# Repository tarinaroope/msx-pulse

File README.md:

# msx-pulse

A diagnostic cartridge for MSX computers. Very much a work in progress. This is at
proof-of-concept stage. It boots, it reads the bus, it tells you things, but it's a
long way from a finished product. I'm building it partly because I wanted an "is this
MSX dead, and if so why" tool, and partly to learn, so expect rough edges.

## What it does today

Plug it into the cartridge slot and it sits there passively. It doesn't drive the bus,
so it's safe to leave in while the MSX powers up on its own. While it watches, it
reports on a small OLED:

- the +5V, +12V and −12V rails
- whether the 3.58 MHz clock is alive and roughly the right frequency
- the state of /RESET
- what the address and data lines are doing, including bits that look stuck or are
  never driven

It can also pulse /RESET and follow the early boot sequence to see how far the machine
gets. There's a USB serial log too if you want the detail on a host.

That's already enough to tell, say, a dead clock apart from dead RAM without pulling
the machine apart. I'm still working out the full list of faults it can sensibly
diagnose and a lot of that will come from pointing it at actually-broken machines and
seeing what shows up.

## What's next

The next goal is to have the cartridge *serve* a diagnostic ROM to the MSX and act as
the boot ROM itself and run Z80 test code on the machine's own CPU, the way the Dead
Test cart does. The firmware already has the groundwork for this (it can emulate a ROM
on the bus), but turning that into a proper guided test sequence is the next chunk of
work. The passive monitoring above is the part that somewhat works.

## Hardware

Fair warning: I'm a software person, not a hardware engineer, and this board is one of
the first things I've designed. It's a quick first cut to get *something* I could test
firmware against, and it shows. There's a KiCad project in [`hardware/`](hardware/)
(schematics, PCB, gerbers) and a parts list in [`docs/BOM.csv`](docs/BOM.csv) — read
them as "what I actually had made", not "the right way to do this".

The brain is a bare RP2354B (the QFN-80 part, 48 GPIO, 2 MB internal flash) wired onto
the cartridge edge connector and powered from the slot. The current board puts 74LVC245
level shifters on just about every bus line. Having lived with it, I think that's
overkill... the address and control inputs could most likely get by with plain series
resistors and no shifters. The data lines are the exception: those are bidirectional
and actually get driven, so keeping real level shifting there still makes sense, mostly
for protection.

Things I'd like to change in the next board revision:

- drop the level shifters on the address/control inputs, keep them on D0–D7
- shrink the PCB to fit an actual MSX cartridge shell (it's oversized right now)
- swap the ADC protection diodes as I miscalculated the zeners, seems it works even better without.
- a bigger power-on-reset cap for a more reliable cold boot
- a normal 2.54 mm SWD header (plus a UART header which I omitted) instead of the fine-pitch one I used

## Building

You'll need the Arm GNU toolchain (`arm-none-eabi`), the Raspberry Pi Pico SDK, and
sjasmplus for the Z80 side.

```sh
export PICO_SDK_PATH=/path/to/pico-sdk
cmake -S . -B build -DPICO_TOOLCHAIN_PATH=/path/to/arm-none-eabi/bin
cmake --build build -j
```

Out comes:

- `build/src/firmware/msxdoc.uf2` — the firmware
- `build/diag.rom` — the Z80 test ROM, assembled and baked into the firmware for you (not served) 

## Flashing

Hold BOOTSEL, plug into USB, and drop the `.uf2` onto the drive that appears. Or, with
picotool:

```sh
picotool load -x build/src/firmware/msxdoc.uf2
```

Or via swd.

## Layout

```
src/rom/        Z80 test ROM (sjasmplus)
src/firmware/   RP2354B firmware (pico-sdk, C + PIO)
hardware/       KiCad schematics, PCB, gerbers
docs/           bill of materials
```

## License

MIT — see [LICENSE](LICENSE).

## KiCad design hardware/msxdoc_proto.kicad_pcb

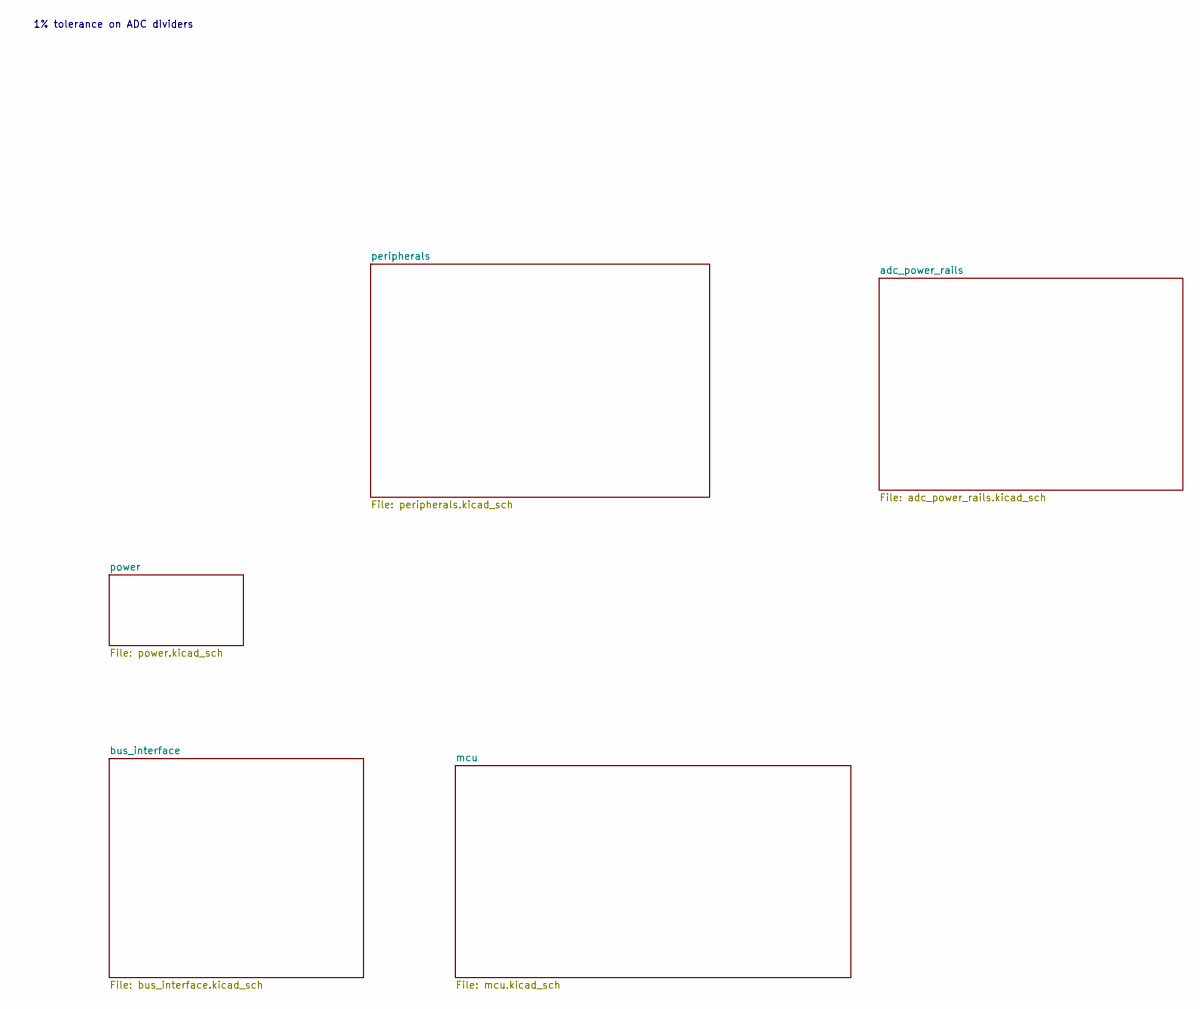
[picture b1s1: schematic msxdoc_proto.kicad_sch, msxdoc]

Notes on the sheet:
1% tolerance on ADC dividers

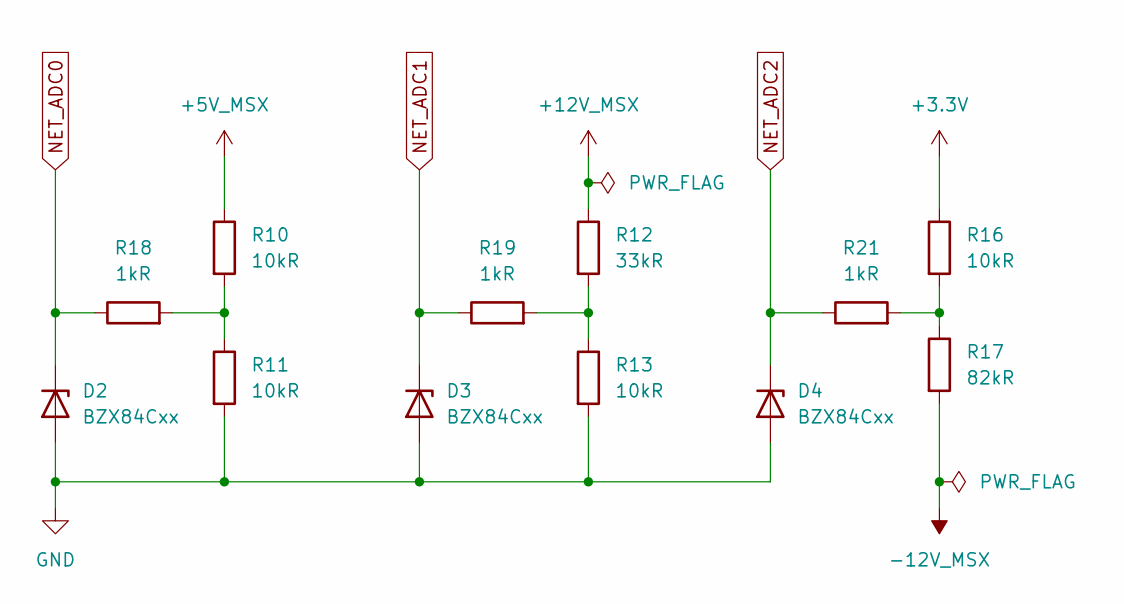
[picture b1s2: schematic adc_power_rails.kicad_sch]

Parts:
D2, D3, D4: BZX84Cxx; SOT-23
R10, R11, R13, R16: 10kR; R_0603_1608Metric
R12: 33kR; R_0603_1608Metric
R17: 82kR; R_0603_1608Metric
R18, R19, R21: 1kR; R_0603_1608Metric

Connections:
+3.3V: R16.1; also elsewhere on the board
+5V_MSX: R10.1; also elsewhere on the board
+12V_MSX: R12.1; also elsewhere on the board
-12V_MSX: R17.2; also elsewhere on the board
GND: D2.1 (A), D3.1 (A), D4.1 (A), R11.2, R13.2; also elsewhere on the board
NET_ADC0: D2.3 (K), R18.1; also elsewhere on the board
NET_ADC1: D3.3 (K), R19.1; also elsewhere on the board
NET_ADC2: D4.3 (K), R21.1; also elsewhere on the board
unnamed: R10.2, R11.1, R18.2
unnamed: R12.2, R13.1, R19.2
unnamed: R16.2, R17.1, R21.2

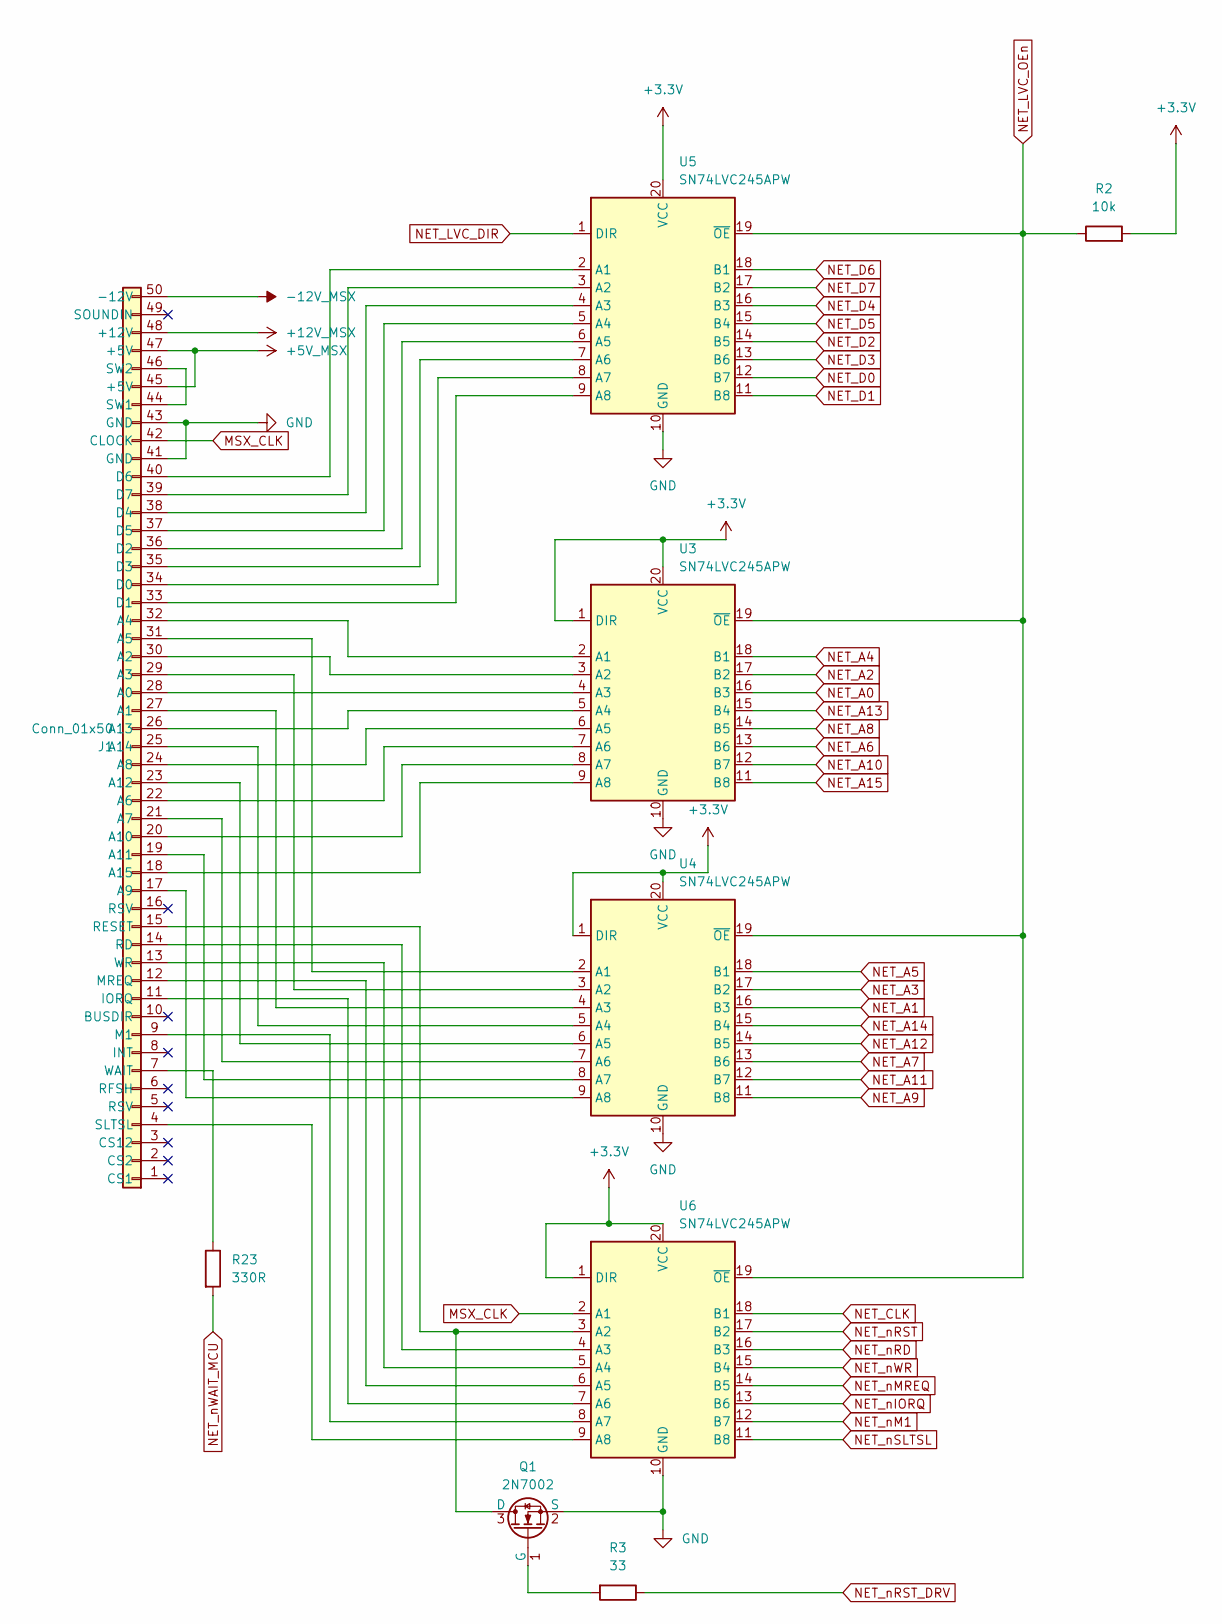
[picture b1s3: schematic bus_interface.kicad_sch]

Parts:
J1: Conn_01x50; MSX-EDGE
Q1: 2N7002; SOT-23; LCSC C81445
R2: 10k; R_0603_1608Metric
R3: 33; R_0603_1608Metric
R23: 330R; R_0603_1608Metric
U3, U4, U5, U6: SN74LVC245APW; TSSOP-20_4.4x6.5mm_P0.65mm; LCSC C7848

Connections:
+3.3V: R2.2, U3.1 (DIR), U3.20 (VCC), U4.1 (DIR), U4.20 (VCC), U5.20 (VCC), U6.1 (DIR), U6.20 (VCC); also elsewhere on the board
+5V_MSX: J1.45 (+5V), J1.47 (+5V); also elsewhere on the board
+12V_MSX: J1.48 (+12V); also elsewhere on the board
-12V_MSX: J1.50 (-12V); also elsewhere on the board
GND: J1.41 (GND), J1.43 (GND), Q1.2 (S), U3.10 (GND), U4.10 (GND), U5.10 (GND), U6.10 (GND); also elsewhere on the board
MSX_CLK: J1.42 (CLOCK), U6.2 (A1)
NET_A0: U3.16 (B3); also elsewhere on the board
NET_A1: U4.16 (B3); also elsewhere on the board
NET_A2: U3.17 (B2); also elsewhere on the board
NET_A3: U4.17 (B2); also elsewhere on the board
NET_A4: U3.18 (B1); also elsewhere on the board
NET_A5: U4.18 (B1); also elsewhere on the board
NET_A6: U3.13 (B6); also elsewhere on the board
NET_A7: U4.13 (B6); also elsewhere on the board
NET_A8: U3.14 (B5); also elsewhere on the board
NET_A9: U4.11 (B8); also elsewhere on the board
NET_A10: U3.12 (B7); also elsewhere on the board
NET_A11: U4.12 (B7); also elsewhere on the board
NET_A12: U4.14 (B5); also elsewhere on the board
NET_A13: U3.15 (B4); also elsewhere on the board
NET_A14: U4.15 (B4); also elsewhere on the board
NET_A15: U3.11 (B8); also elsewhere on the board
NET_CLK: U6.18 (B1); also elsewhere on the board
NET_D0: U5.12 (B7); also elsewhere on the board
NET_D1: U5.11 (B8); also elsewhere on the board
NET_D2: U5.14 (B5); also elsewhere on the board
NET_D3: U5.13 (B6); also elsewhere on the board
NET_D4: U5.16 (B3); also elsewhere on the board
NET_D5: U5.15 (B4); also elsewhere on the board
NET_D6: U5.18 (B1); also elsewhere on the board
NET_D7: U5.17 (B2); also elsewhere on the board
NET_LVC_DIR: U5.1 (DIR); also elsewhere on the board
NET_LVC_OEn: R2.1, U3.19 (~OE), U4.19 (~OE), U5.19 (~OE), U6.19 (~OE); also elsewhere on the board
NET_nIORQ: U6.13 (B6); also elsewhere on the board
NET_nM1: U6.12 (B7); also elsewhere on the board
NET_nMREQ: U6.14 (B5); also elsewhere on the board
NET_nRD: U6.16 (B3); also elsewhere on the board
NET_nRST: U6.17 (B2); also elsewhere on the board
NET_nRST_DRV: R3.1; also elsewhere on the board
NET_nSLTSL: U6.11 (B8); also elsewhere on the board
NET_nWAIT_MCU: R23.2; also elsewhere on the board
NET_nWR: U6.15 (B4); also elsewhere on the board
unnamed: J1.28 (A0), U3.4 (A3)
unnamed: J1.27 (A1), U4.4 (A3)
unnamed: J1.30 (A2), U3.3 (A2)
unnamed: J1.29 (A3), U4.3 (A2)
unnamed: J1.32 (A4), U3.2 (A1)
unnamed: J1.31 (A5), U4.2 (A1)
unnamed: J1.22 (A6), U3.7 (A6)
unnamed: J1.21 (A7), U4.7 (A6)
unnamed: J1.24 (A8), U3.6 (A5)
unnamed: J1.17 (A9), U4.9 (A8)
unnamed: J1.20 (A10), U3.8 (A7)
unnamed: J1.19 (A11), U4.8 (A7)
unnamed: J1.23 (A12), U4.6 (A5)
unnamed: J1.26 (A13), U3.5 (A4)
unnamed: J1.25 (A14), U4.5 (A4)
unnamed: J1.18 (A15), U3.9 (A8)
unnamed: J1.34 (D0), U5.8 (A7)
unnamed: J1.33 (D1), U5.9 (A8)
unnamed: J1.36 (D2), U5.6 (A5)
unnamed: J1.35 (D3), U5.7 (A6)
unnamed: J1.38 (D4), U5.4 (A3)
unnamed: J1.37 (D5), U5.5 (A4)
unnamed: J1.40 (D6), U5.2 (A1)
unnamed: J1.39 (D7), U5.3 (A2)
unnamed: J1.11 (IORQ), U6.7 (A6)
unnamed: J1.9 (M1), U6.8 (A7)
unnamed: J1.12 (MREQ), U6.6 (A5)
unnamed: J1.14 (RD), U6.4 (A3)
unnamed: J1.15 (RESET), Q1.3 (D), U6.3 (A2)
unnamed: J1.4 (SLTSL), U6.9 (A8)
unnamed: J1.44 (SW1), J1.46 (SW2)
unnamed: J1.7 (WAIT), R23.1
unnamed: J1.13 (WR), U6.5 (A4)
unnamed: Q1.1 (G), R3.2

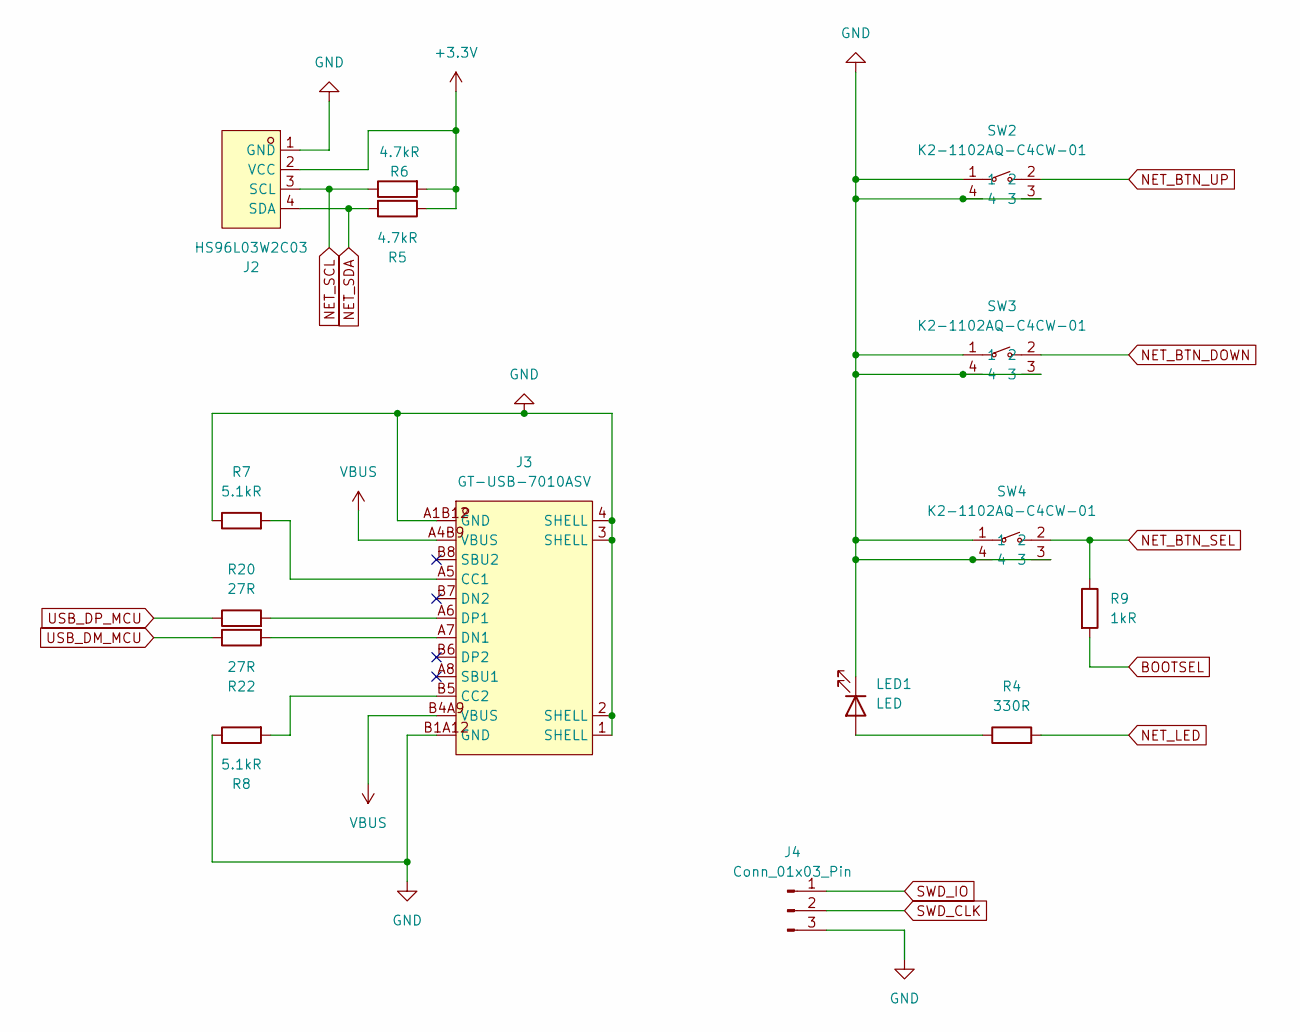
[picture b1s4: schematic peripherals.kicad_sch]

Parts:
J2: HS96L03W2C03; OLED-TH_L27.8-W27.2-P2.54_C9900033791; MPN HS96L03W2C03; LCSC Part C5248080
J3: GT-USB-7010ASV; USB-C-SMD_G-SWITCH_GT-USB-7010ASV; MPN GT-USB-7010ASV; LCSC Part C2988369
J4: Conn_01x03_Pin; PinHeader_1x03_P2.54mm_Vertical
LED1: LED; LED_0603_1608Metric
R4: 330R; R_0603_1608Metric
R5, R6: 4.7kR; R_0603_1608Metric
R7, R8: 5.1kR; R_0603_1608Metric
R9: 1kR; R_0603_1608Metric
R20, R22: 27R; R_0603_1608Metric
SW2, SW3, SW4: K2-1102AQ-C4CW-01; SW-TH_K2-1102AQ-C4CW-01; MPN K2-1102AQ-C4CW-01; LCSC Part C127680

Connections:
+3.3V: J2.2 (VCC), R5.1, R6.2; also elsewhere on the board
BOOTSEL: R9.2; also elsewhere on the board
GND: J2.1 (GND), J3.1 (SHELL), J3.2 (SHELL), J3.3 (SHELL), J3.4 (SHELL), J3.A1B12 (GND), J3.B1A12 (GND), J4.3, LED1.1 (K), R7.1, R8.1, SW2.1, SW2.3, SW2.4, SW3.1, SW3.3, SW3.4, SW4.1, SW4.3, SW4.4; also elsewhere on the board
NET_BTN_DOWN: SW3.2; also elsewhere on the board
NET_BTN_SEL: R9.1, SW4.2; also elsewhere on the board
NET_BTN_UP: SW2.2; also elsewhere on the board
NET_LED: R4.2; also elsewhere on the board
NET_SCL: J2.3 (SCL), R6.1; also elsewhere on the board
NET_SDA: J2.4 (SDA), R5.2; also elsewhere on the board
unnamed: J3.A5 (CC1), R7.2
unnamed: J3.B5 (CC2), R8.2
unnamed: J3.A7 (DN1), R22.2
unnamed: J3.A6 (DP1), R20.2
unnamed: LED1.2 (A), R4.1
SWD_CLK: J4.2; also elsewhere on the board
SWD_IO: J4.1; also elsewhere on the board
USB_DM_MCU: R22.1; also elsewhere on the board
USB_DP_MCU: R20.1; also elsewhere on the board
VBUS: J3.A4B9 (VBUS), J3.B4A9 (VBUS); also elsewhere on the board

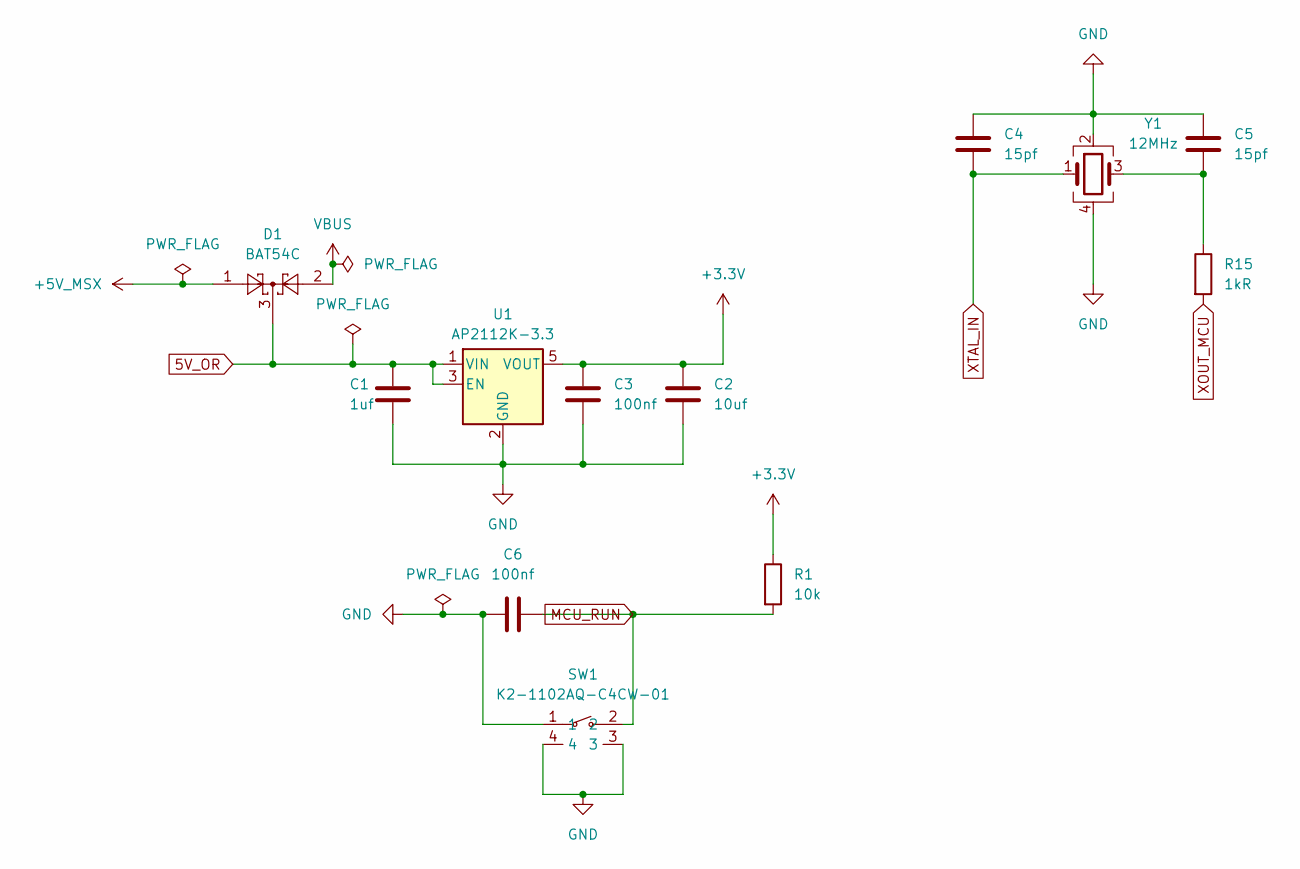
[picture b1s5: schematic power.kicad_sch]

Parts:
C1: 1uf; C_0603_1608Metric
C2: 10uf; C_0603_1608Metric
C3, C6: 100nf; C_0603_1608Metric
C4, C5: 15pf; C_0603_1608Metric
D1: BAT54C; SOT-23; LCSC C37704
R1: 10k; R_0603_1608Metric
R15: 1kR; R_0603_1608Metric
SW1: K2-1102AQ-C4CW-01; SW-TH_K2-1102AQ-C4CW-01; MPN K2-1102AQ-C4CW-01; LCSC Part C127680
U1: AP2112K-3.3; SOT-23-5; LCSC C23380830
Y1: 12MHz; Crystal_SMD_3225-4Pin_3.2x2.5mm; LCSC part C20625731

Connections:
5V_OR: C1.1, D1.3, U1.1 (VIN), U1.3 (EN)
+3.3V: C2.1, C3.1, R1.1, U1.5 (VOUT); also elsewhere on the board
+5V_MSX: D1.1; also elsewhere on the board
GND: C1.2, C2.2, C3.2, C4.1, C5.1, C6.1, SW1.1, SW1.3, SW1.4, U1.2 (GND), Y1.2, Y1.4; also elsewhere on the board
MCU_RUN: C6.2, R1.2, SW1.2; also elsewhere on the board
unnamed: C5.2, R15.1, Y1.3
VBUS: D1.2; also elsewhere on the board
XOUT_MCU: R15.2; also elsewhere on the board
XTAL_IN: C4.2, Y1.1; also elsewhere on the board

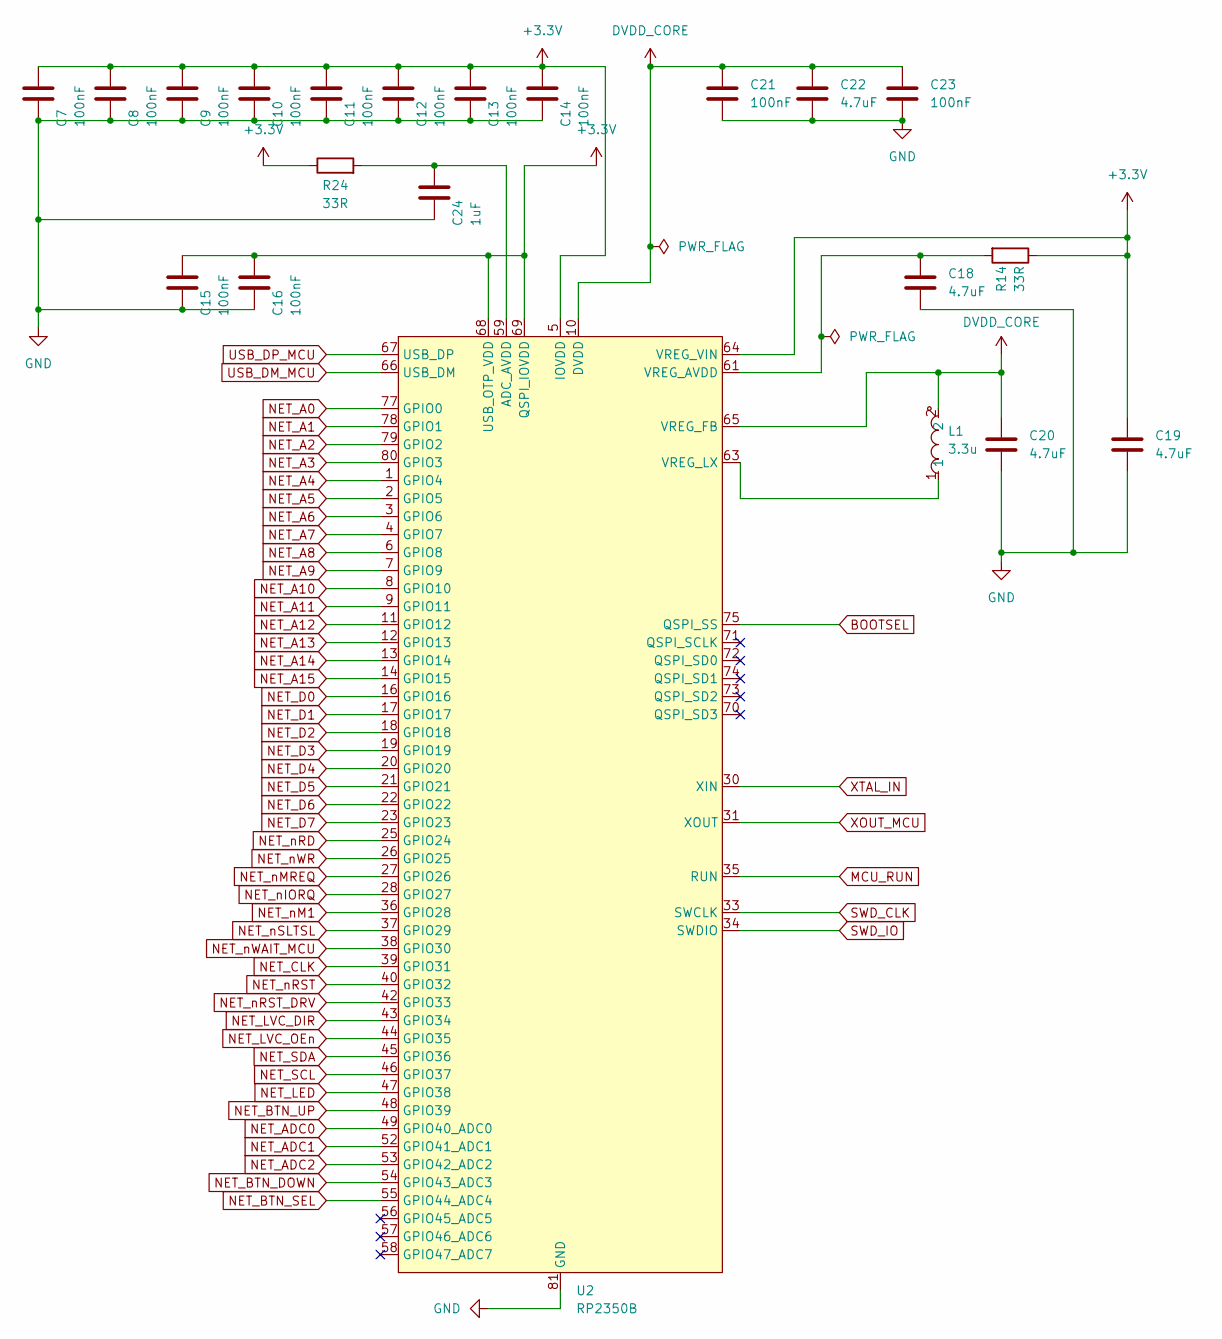
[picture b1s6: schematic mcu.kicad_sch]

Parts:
C7, C8, C9, C10, C11, C12, C13, C14, C15, C16, C21, C23: 100nF; C_0402_1005Metric
C18, C19, C20, C22: 4.7uF; C_0402_1005Metric
C24: 1uF; C_0402_1005Metric
L1: 3.3u; IND-SMD_L2.0-W1.6_AOTA-B201610S3R3-101-T; MPN AOTA-B201610S3R3-101-T; LCSC Part C42411119
R14, R24: 33R; R_0603_1608Metric
U2: RP2350B; QFN-80-1EP_10x10mm_P0.4mm_EP3.4x3.4mm_ThermalVias

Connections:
+3.3V: C7.1, C8.1, C9.1, C10.1, C11.1, C12.1, C13.1, C14.1, C15.1, C16.1, C19.1, R14.1, R24.1, U2.5 (IOVDD), U2.15 (IOVDD), U2.24 (IOVDD), U2.29 (IOVDD), U2.41 (IOVDD), U2.50 (IOVDD), U2.60 (IOVDD), U2.64 (VREG_VIN), U2.68 (USB_OTP_VDD), U2.69 (QSPI_IOVDD), U2.76 (IOVDD); also elsewhere on the board
BOOTSEL: U2.75 (QSPI_SS); also elsewhere on the board
DVDD_CORE: C20.1, C21.1, C22.1, C23.1, L1.2, U2.10 (DVDD), U2.32 (DVDD), U2.51 (DVDD), U2.65 (VREG_FB)
GND: C7.2, C8.2, C9.2, C10.2, C11.2, C12.2, C13.2, C14.2, C15.2, C16.2, C18.2, C19.2, C20.2, C21.2, C22.2, C23.2, C24.2, U2.62 (VREG_PGND), U2.81 (GND); also elsewhere on the board
MCU_RUN: U2.35 (RUN); also elsewhere on the board
NET_A0: U2.77 (GPIO0); also elsewhere on the board
NET_A1: U2.78 (GPIO1); also elsewhere on the board
NET_A2: U2.79 (GPIO2); also elsewhere on the board
NET_A3: U2.80 (GPIO3); also elsewhere on the board
NET_A4: U2.1 (GPIO4); also elsewhere on the board
NET_A5: U2.2 (GPIO5); also elsewhere on the board
NET_A6: U2.3 (GPIO6); also elsewhere on the board
NET_A7: U2.4 (GPIO7); also elsewhere on the board
NET_A8: U2.6 (GPIO8); also elsewhere on the board
NET_A9: U2.7 (GPIO9); also elsewhere on the board
NET_A10: U2.8 (GPIO10); also elsewhere on the board
NET_A11: U2.9 (GPIO11); also elsewhere on the board
NET_A12: U2.11 (GPIO12); also elsewhere on the board
NET_A13: U2.12 (GPIO13); also elsewhere on the board
NET_A14: U2.13 (GPIO14); also elsewhere on the board
NET_A15: U2.14 (GPIO15); also elsewhere on the board
NET_ADC0: U2.49 (GPIO40_ADC0); also elsewhere on the board
NET_ADC1: U2.52 (GPIO41_ADC1); also elsewhere on the board
NET_ADC2: U2.53 (GPIO42_ADC2); also elsewhere on the board
NET_BTN_DOWN: U2.54 (GPIO43_ADC3); also elsewhere on the board
NET_BTN_SEL: U2.55 (GPIO44_ADC4); also elsewhere on the board
NET_BTN_UP: U2.48 (GPIO39); also elsewhere on the board
NET_CLK: U2.39 (GPIO31); also elsewhere on the board
NET_D0: U2.16 (GPIO16); also elsewhere on the board
NET_D1: U2.17 (GPIO17); also elsewhere on the board
NET_D2: U2.18 (GPIO18); also elsewhere on the board
NET_D3: U2.19 (GPIO19); also elsewhere on the board
NET_D4: U2.20 (GPIO20); also elsewhere on the board
NET_D5: U2.21 (GPIO21); also elsewhere on the board
NET_D6: U2.22 (GPIO22); also elsewhere on the board
NET_D7: U2.23 (GPIO23); also elsewhere on the board
NET_LED: U2.47 (GPIO38); also elsewhere on the board
NET_LVC_DIR: U2.43 (GPIO34); also elsewhere on the board
NET_LVC_OEn: U2.44 (GPIO35); also elsewhere on the board
NET_SCL: U2.46 (GPIO37); also elsewhere on the board
NET_SDA: U2.45 (GPIO36); also elsewhere on the board
NET_nIORQ: U2.28 (GPIO27); also elsewhere on the board
NET_nM1: U2.36 (GPIO28); also elsewhere on the board
NET_nMREQ: U2.27 (GPIO26); also elsewhere on the board
NET_nRD: U2.25 (GPIO24); also elsewhere on the board
NET_nRST: U2.40 (GPIO32); also elsewhere on the board
NET_nRST_DRV: U2.42 (GPIO33); also elsewhere on the board
NET_nSLTSL: U2.37 (GPIO29); also elsewhere on the board
NET_nWAIT_MCU: U2.38 (GPIO30); also elsewhere on the board
NET_nWR: U2.26 (GPIO25); also elsewhere on the board
unnamed: C24.1, R24.2, U2.59 (ADC_AVDD)
unnamed: C18.1, R14.2, U2.61 (VREG_AVDD)
unnamed: L1.1, U2.63 (VREG_LX)
SWD_CLK: U2.33 (SWCLK); also elsewhere on the board
SWD_IO: U2.34 (SWDIO); also elsewhere on the board
USB_DM_MCU: U2.66 (USB_DM); also elsewhere on the board
USB_DP_MCU: U2.67 (USB_DP); also elsewhere on the board
XOUT_MCU: U2.31 (XOUT); also elsewhere on the board
XTAL_IN: U2.30 (XIN); also elsewhere on the board

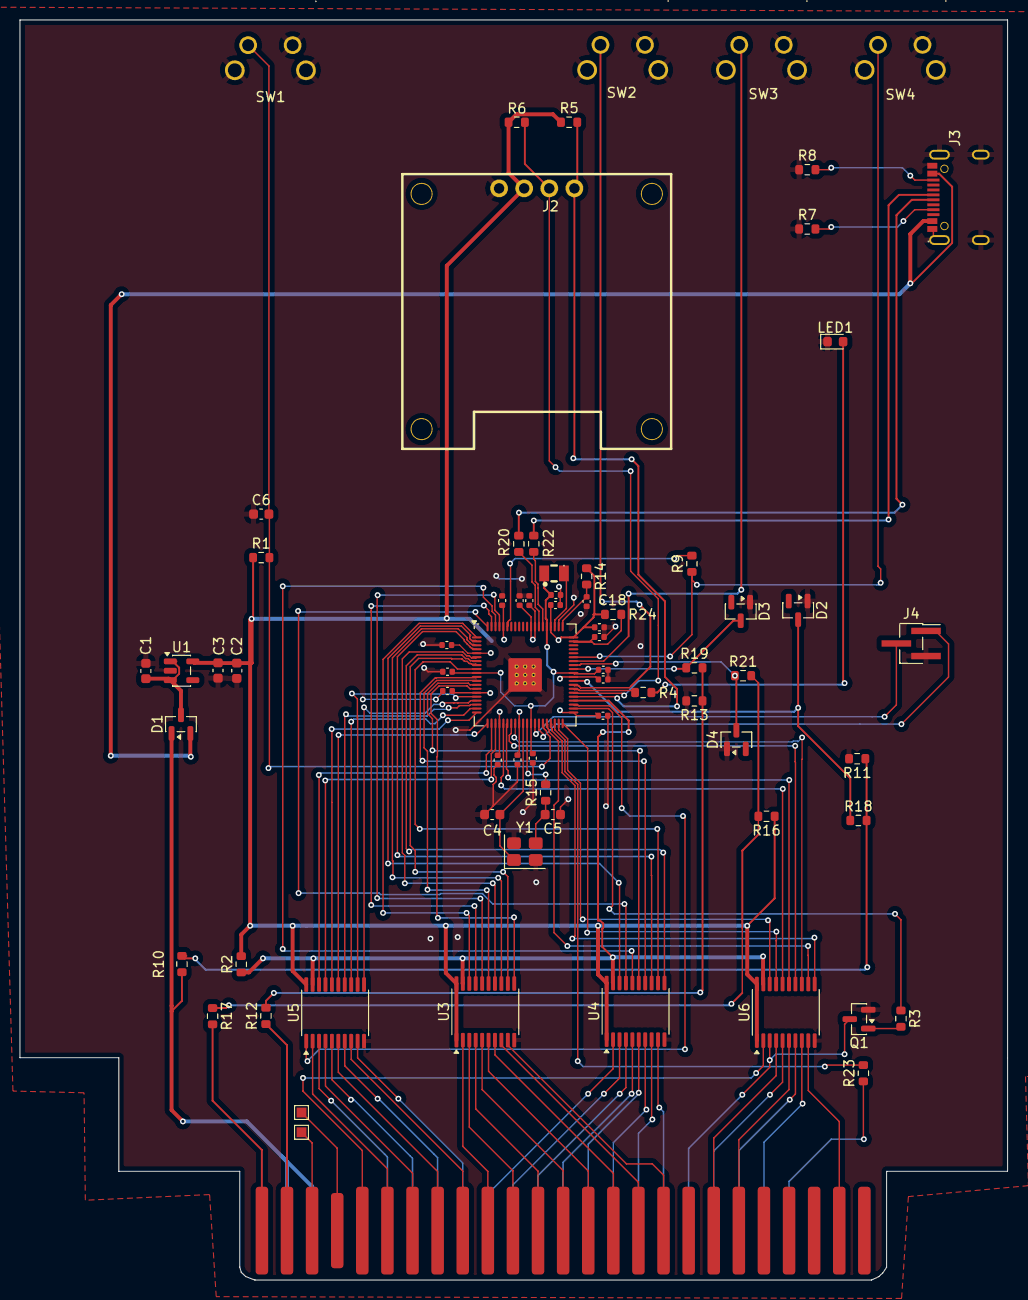
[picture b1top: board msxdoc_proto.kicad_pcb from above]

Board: 2 copper layers, 99.9 x 127.5 mm, 69 parts (0 on the bottom side), 108 nets.

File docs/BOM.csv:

Designator,Qty,Value,Package,Description,MPN / Note,LCSC Part #
U2,1,RP2354B,QFN-80,"MCU — ROM emulator, bus monitor, output controller",Raspberry Pi RP2354B,
U1,1,AP2112K-3.3,SOT-23-5,"LDO 600mA, 3.3V fixed output",Diodes AP2112K-3.3TRG1,
"U3, U4, U5, U6",4,74LVC245,SOIC-20,"Octal bus transceiver, 5V tolerant, 3.3V VCC",TI SN74LVC245ADWR or equiv,
L1,1,"3.3µH, Abracon AOTA-B201610S3R3-101-T",0806 (2016 metric),SMPS inductor — polarity dot CRITICAL; use this exact part,Abracon AOTA-B201610S3R3-101-T,
D1,1,BAT54C,SOT-23,"Dual Schottky, common cathode — power OR circuit","Nexperia BAT54C,215",
"D2, D3, D4",3,BZX84-C3V3,SOT-23,"3.3V Zener — ADC input overvoltage clamp. [SPIN-2: replace with PESD3V3L1BA SOT-23, see KNOWN_RISKS L7]","Nexperia BZX84-C3V3,235 or equiv",
Q1,1,2N7002,SOT-23,N-MOSFET — MSX /RESET drive,"Nexperia 2N7002,235 or equiv",
Y1,1,12MHz crystal,3225 SMD,Crystal — USB and PIO timing; ABM8-272-T3 recommended,Abracon ABM8-272-T3 (recommended) or equiv 12MHz 10pF 50Ω ESR,
"R20, R22",2,27Ω,0603 5%,USB DP/DM series termination — place close to MCU,,
"R3, R14, R24",3,33Ω,0603 5%,2N7002 gate damper (R3) + VREG_AVDD filter (R14) + ADC_AVDD filter (R24),,
"R4, R23",2,330Ω,0603 5%,"LED current limiter (R4), /WAIT series protection (R23)",,
"R9, R15, R18, R19, R21",5,1kΩ,0603 5%,"BOOTSEL isolation, crystal XOUT damping, ADC series protection",,
"R1, R2",2,10kΩ,0603 5%,RUN pin pull-up (R1) + 74LVC245 /OE pull-up (R2),,
"R5, R6",2,4.7kΩ,0603 5%,I2C SDA + SCL pull-ups,,
"R7, R8",2,5.1kΩ,0603 5%,USB-C CC1 + CC2 pull-downs,,
"R10, R11, R13, R16",4,10kΩ,0603 1%,ADC voltage dividers (1% required for rail measurement accuracy),,
R12,1,33kΩ,0603 1%,+12V rail divider (high side),,
R17,1,82kΩ,0603 1%,−12V bridge divider (low side),,
"C4, C5",2,15pF C0G/NP0,0603,Crystal load caps — C0G/NP0 mandatory,,
C1,1,1µF X5R 6.3V,0603,LDO VIN bypass,,
C2,1,10µF X5R 6.3V,0603,LDO output bulk cap,,
C24,1,1µF X5R 6.3V,0402,ADC_AVDD filter cap,,
"C18, C19, C20",3,4.7µF X5R 6.3V,0402,"VREG: AVDD filter cap (C18), VIN bypass (C19), DVDD output (C20)",,
"C3, C6",2,100nF X7R 10V,0603,"Decoupling: LDO local (C3), reset RC (C6)",,
"C7, C8, C9, C10, C11, C12, C13, C14, C15, C16, C21, C22, C23",13,100nF X7R 10V,0402,"MCU decoupling: IOVDD (×8, C7–C14), QSPI/USB (×2, C15–C16), DVDD (×3, C21–C23)",,
J3,1,GCT USB4085,mid-mount SMD,USB-C receptacle — firmware update + serial log,GCT USB4085-GF-A,
J4,1,SWD 3-pin header,1.27mm pitch SMD,SWD debug: SWDIO / SWDCLK / GND,,
J2,1,4-pin 2.54mm header,through-hole,"OLED mounting header (SDA, SCL, GND, 3.3V)",,
"SW1, SW2, SW3, SW4",4,6×6mm SMD tactile,SMD,"Buttons: RESET (SW1), UP (SW2), DOWN (SW3), SELECT (SW4)",C&K PTS645SK43SMTR92 LFS or equiv,
LED1,1,Green LED,0603,Firmware-driven status LED (GP38 via R4). Not a passive power indicator.,,

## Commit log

2026-06-05 Sync 2026-06-05: initial release
2026-06-06 Sync 2026-06-06
